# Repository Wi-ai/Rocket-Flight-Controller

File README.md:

# Rocket-Flight-Controller
this is a prototype flight controller for the rocket am building

Shipping price

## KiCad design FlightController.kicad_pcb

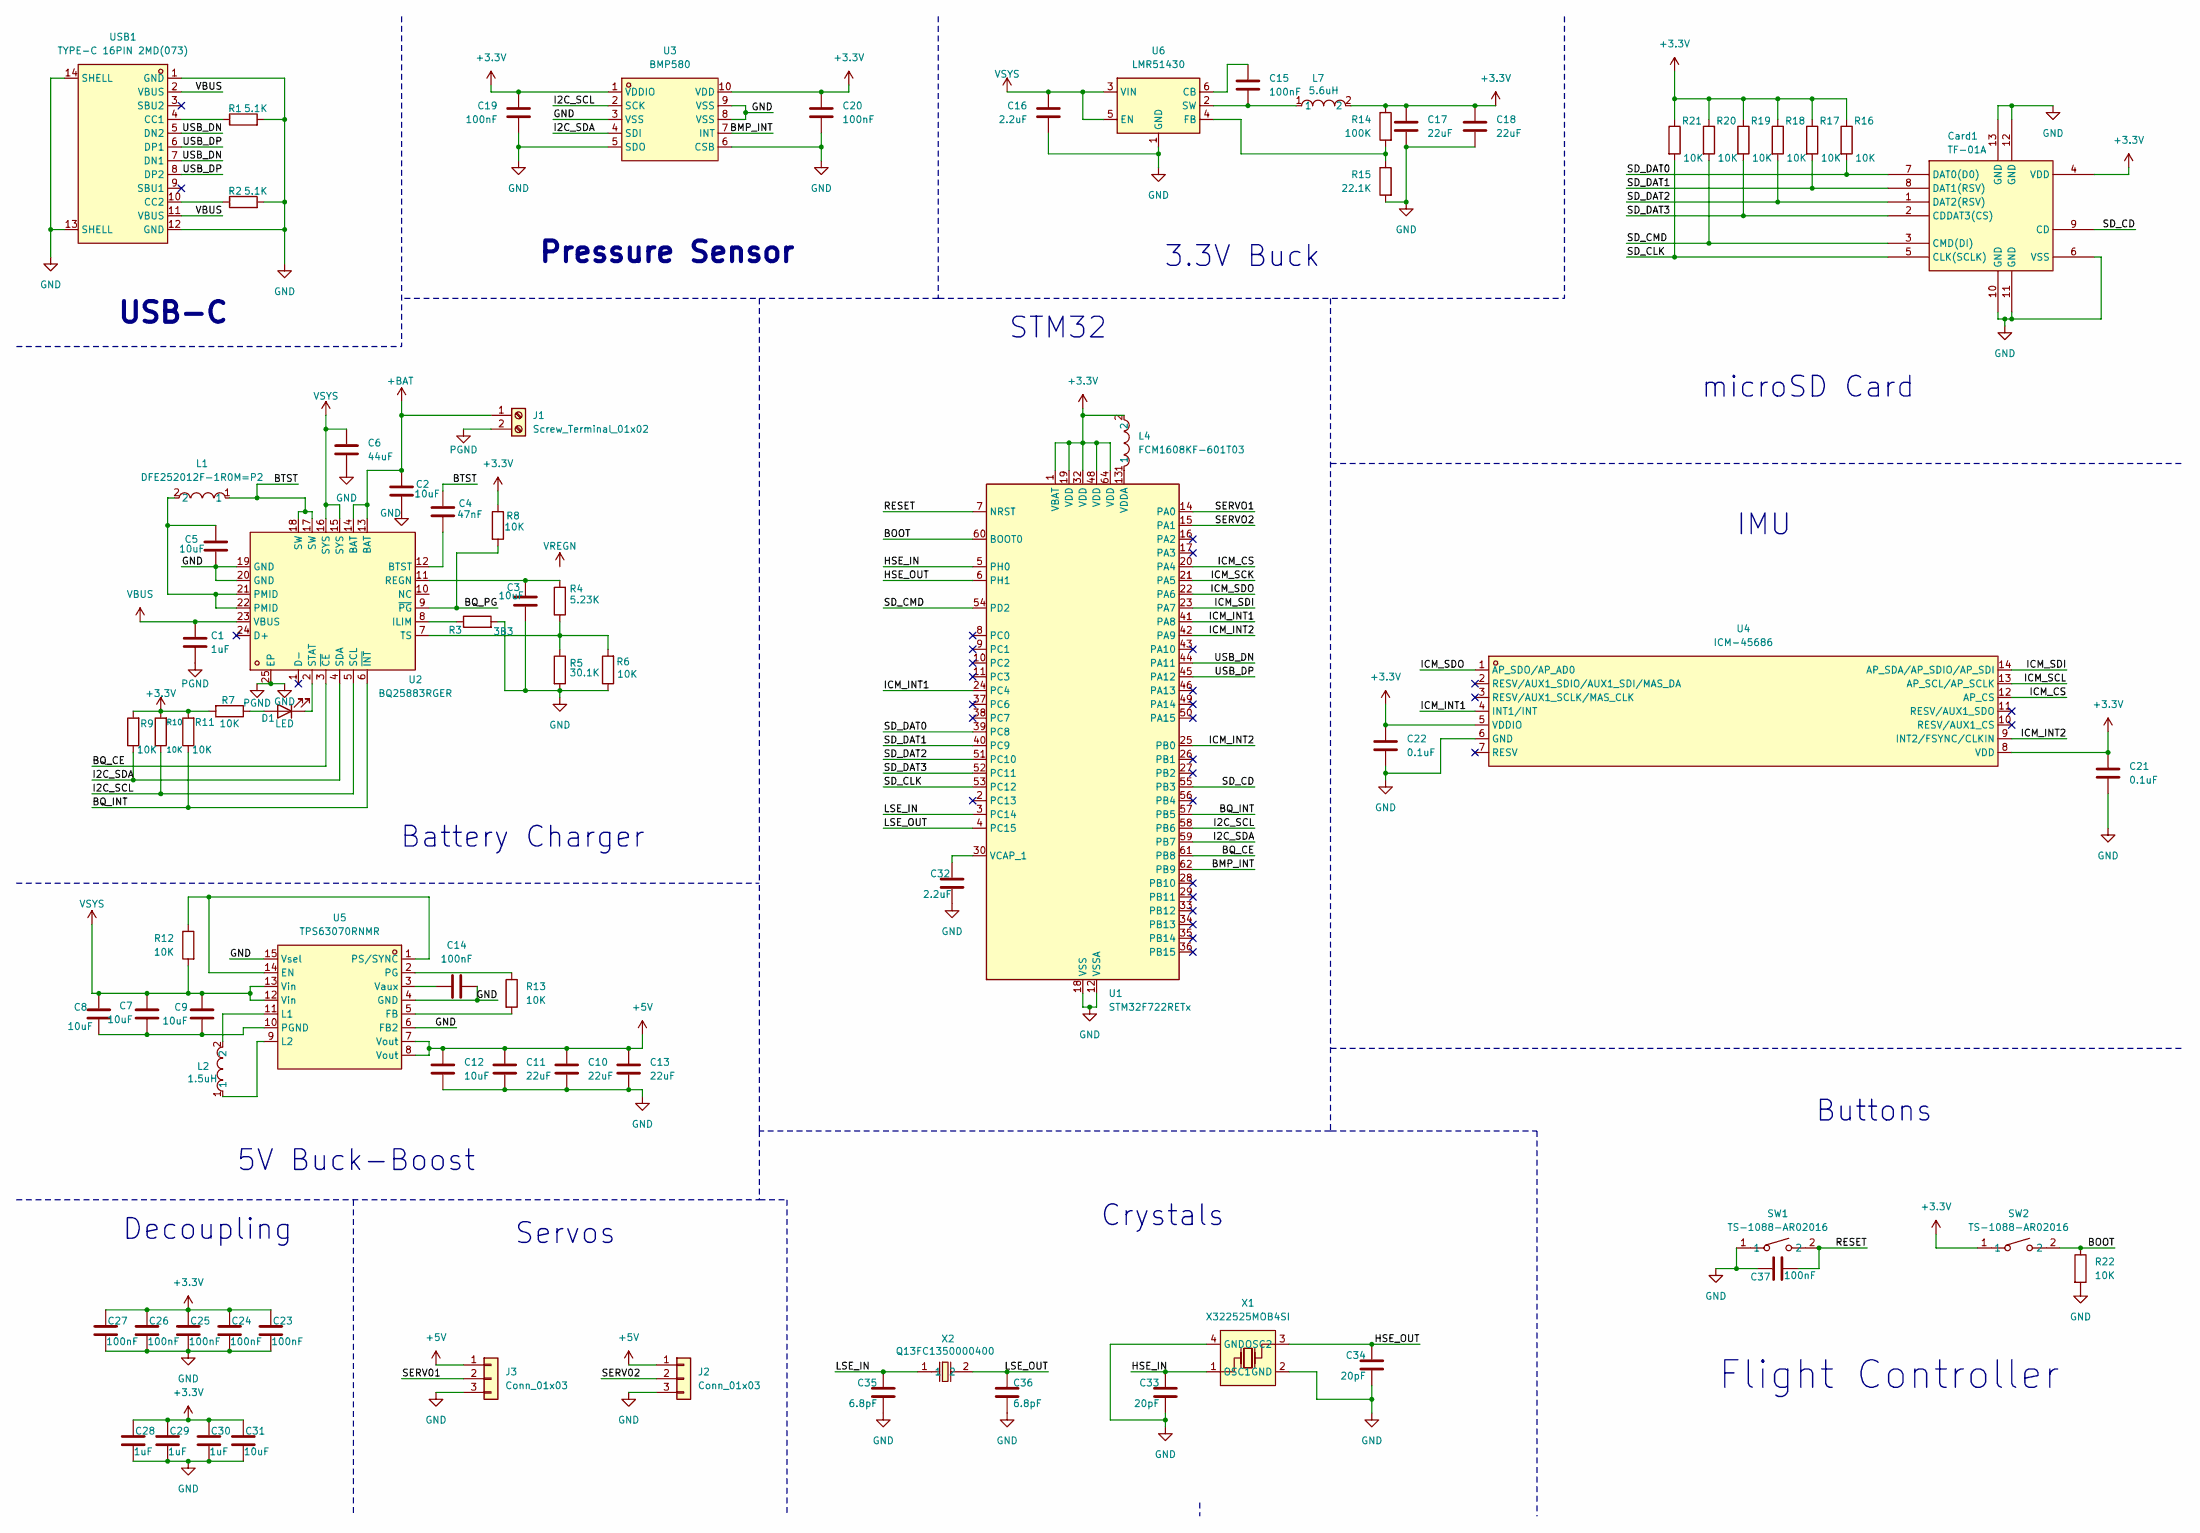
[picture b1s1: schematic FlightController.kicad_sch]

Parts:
C1, C28, C29, C30: 1uF; C_0402_1005Metric
C2, C9, C12: 10uF; C_0603_1608Metric
C3, C5, C31: 10uF; C_0402_1005Metric
C4: 47nF; C_0201_0603Metric
C6: 44uF; C_0603_1608Metric
C7, C8: 10uF; C_0805_2012Metric
C10, C11, C13: 22uF; C_0805_2012Metric
C14, C15, C19, C20, C23, C24, C25, C26, C27, C37: 100nF; C_0201_0603Metric
C16: 2.2uF; C_0603_1608Metric
C17, C18: 22uF; C_0402_1005Metric
C21, C22: 0.1uF; C_0201_0603Metric
C32: 2.2uF; C_0201_0603Metric
C33, C34: 20pF; C_0201_0603Metric
C35, C36: 6.8pF; C_0201_0603Metric
Card1: TF-01A; TF-SMD_TF-01A; LCSC Part C91145
D1: LED; LED_0402_1005Metric
J1: Screw_Terminal_01x02; TerminalBlock_Xinya_XY308-2.54-2P_1x02_P2.54mm_Horizontal
J2, J3: Conn_01x03; PinHeader_1x03_P2.54mm_Vertical
L1: DFE252012F-1R0M=P2; L2520; LCSC Part C435392
L2: 1.5uH; IND-SMD_L4.0-W4.0-A; LCSC Part C3033018
L4: FCM1608KF-601T03; L0603; LCSC Part C141723
L7: 5.6uH; IND-SMD_L3.0-W3.0; LCSC Part C18236327
R1, R2: 5.1K; R_0201_0603Metric
R3: 3B3; R_0201_0603Metric
R4: 5.23K; R_0201_0603Metric
R5: 30.1K; R_0201_0603Metric
R6, R7, R8, R9, R10, R11, R12, R13, R16, R17, R18, R19, R20, R21, R22: 10K; R_0201_0603Metric
R14: 100K; R_0402_1005Metric
R15: 22.1K; R_0402_1005Metric
SW1, SW2: TS-1088-AR02016; SW-SMD_L3.9-W3.0-P4.45; LCSC Part C720477
U1: STM32F722RETx; LQFP-64_10x10mm_P0.5mm
U2: BQ25883RGER; VFQFPN-24_L4.0-W4.0-P0.50-BL-EP2.8; LCSC Part C544362
U3: BMP580; LGA-10_L2.0-W2.0-P0.50-TL_BMP580; LCSC Part C22391138
U4: ICM-45686; LGA-14_L3.0-W2.5-P0.50-TL; LCSC Part C22459454
U5: TPS63070RNMR; VQFN-HR-15_L3.0-W2.5-P0.50-BL_TPS63070RNMR; LCSC Part C109322
U6: LMR51430; SOT-23-6
USB1: TYPE-C 16PIN 2MD(073); USB-C-SMD_TYPE-C-6PIN-2MD-073; LCSC Part C2765186
X1: X322525MOB4SI; CRYSTAL-SMD_4P-L3.2-W2.5-BL; LCSC Part C9006
X2: Q13FC1350000400; FC-135R_L3.2-W1.5; LCSC Part C32346

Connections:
+3.3V: C17.1, C18.1, C19.1, C20.1, C21.1, C22.1, C23.1, C24.1, C25.1, C26.1, C27.1, C28.1, C29.1, C30.1, C31.1, Card1.4 (VDD), L4.2, L7.2, R7.2, R8.1, R9.2, R10.2, R11.2, R14.1, R16.1, R17.1, R18.1, R19.1, R20.1, R21.1, SW2.1, U1.1 (VBAT), U1.19 (VDD), U1.32 (VDD), U1.48 (VDD), U1.64 (VDD), U3.1 (VDDIO), U3.10 (VDD), U4.5 (VDDIO), U4.8 (VDD)
+5V: C10.1, C11.1, C12.1, C13.1, J2.1, J3.1, U5.7 (Vout), U5.8 (Vout)
+BAT: C2.1, J1.1, U2.13 (BAT), U2.14 (BAT)
/BMP_INT: U1.62 (PB9), U3.7 (INT)
/BOOT: R22.1, SW2.2, U1.60 (BOOT0)
/BQ_CE: U1.61 (PB8), U2.3 (~CE)
/BQ_INT: R11.1, U1.57 (PB5), U2.6 (~INT)
/BQ_PG: R8.2, U2.9 (~PG)
/BTST: C4.1, L1.1, U2.17 (SW), U2.18 (SW)
/HSE_IN: C33.1, U1.5 (PH0), X1.1 (OSC1)
/HSE_OUT: C34.1, U1.6 (PH1), X1.3 (OSC2)
/I2C_SCL: R10.1, U1.58 (PB6), U2.5 (SCL), U3.2 (SCK)
/I2C_SDA: R9.1, U1.59 (PB7), U2.4 (SDA), U3.4 (SDI)
/ICM_CS: U1.20 (PA4), U4.12 (AP_CS)
/ICM_INT1: U1.24 (PC4), U1.41 (PA8), U4.4 (INT1/INT)
/ICM_INT2: U1.25 (PB0), U1.42 (PA9), U4.9 (INT2/FSYNC/CLKIN)
/ICM_SCK: U1.21 (PA5)
/ICM_SCL: U4.13 (AP_SCL/AP_SCLK)
/ICM_SDI: U1.23 (PA7), U4.14 (AP_SDA/AP_SDIO/AP_SDI)
/ICM_SDO: U1.22 (PA6), U4.1 (AP_SDO/AP_AD0)
/LSE_IN: C35.1, U1.3 (PC14), X2.1
/LSE_OUT: C36.1, U1.4 (PC15), X2.2
/RESET: C37.2, SW1.2, U1.7 (NRST)
/SD_CD: Card1.9 (CD), U1.55 (PB3)
/SD_CLK: Card1.5 (CLK(SCLK)), R21.2, U1.53 (PC12)
/SD_CMD: Card1.3 (CMD(DI)), R20.2, U1.54 (PD2)
/SD_DAT0: Card1.7 (DAT0(D0)), R16.2, U1.39 (PC8)
/SD_DAT1: Card1.8 (DAT1(RSV)), R17.2, U1.40 (PC9)
/SD_DAT2: Card1.1 (DAT2(RSV)), R18.2, U1.51 (PC10)
/SD_DAT3: Card1.2 (CDDAT3(CS)), R19.2, U1.52 (PC11)
/SERV01: J3.2
/SERV02: J2.2
/SERVO1: U1.14 (PA0)
/SERVO2: U1.15 (PA1)
/USB_DN: U1.44 (PA11), USB1.5 (DN2), USB1.7 (DN1)
/USB_DP: U1.45 (PA12), USB1.6 (DP1), USB1.8 (DP2)
GND: C1.2, C2.2, C3.2, C5.2, C6.2, C10.2, C11.2, C12.2, C13.2, C14.2, C16.2, C17.2, C18.2, C19.2, C20.2, C21.2, C22.2, C23.2, C24.2, C25.2, C26.2, C27.2, C28.2, C29.2, C30.2, C31.2, C32.2, C33.2, C34.2, C35.2, C36.2, C37.1, Card1.6 (VSS), Card1.10 (GND), Card1.11 (GND), Card1.12 (GND), Card1.13 (GND), J1.2, J2.3, J3.3, R1.2, R2.2, R3.2, R5.2, R6.1, R15.2, R22.2, SW1.1, U1.12 (VSSA), U1.18 (VSS), U1.31 (VSS), U1.47 (VSS), U1.63 (VSS), U2.19 (GND), U2.20 (GND), U2.25 (EP), U3.3 (VSS), U3.5 (SDO), U3.6 (CSB), U3.8 (VSS), U3.9 (VSS), U4.6 (GND), U5.4 (GND), U5.6 (FB2), U5.15 (Vsel), U6.1 (GND), USB1.1 (GND), USB1.12 (GND), USB1.13 (SHELL), USB1.14 (SHELL), X1.2 (GND), X1.4 (GND)
unnamed: C5.1, L1.2, U2.21 (PMID), U2.22 (PMID)
unnamed: D1.2 (A), R7.1
unnamed: D1.1 (K), U2.2 (STAT)
unnamed: C32.1, U1.30 (VCAP_1)
unnamed: L4.1, U1.13 (VDDA)
unnamed: C4.2, U2.12 (BTST)
unnamed: R3.1, U2.8 (ILIM)
unnamed: C3.1, R4.2, U2.11 (REGN)
unnamed: R4.1, R5.1, R6.2, U2.7 (TS)
unnamed: R12.1, U5.1 (PS/SYNC), U5.14 (EN)
unnamed: R13.2, U5.5 (FB)
unnamed: L2.2, U5.11 (L1)
unnamed: L2.1, U5.9 (L2)
unnamed: R13.1, U5.2 (PG)
unnamed: C7.2, C8.2, C9.2, U5.10 (PGND)
unnamed: C14.1, U5.3 (Vaux)
unnamed: C15.1, U6.6 (CB)
unnamed: R14.2, R15.1, U6.4 (FB)
unnamed: C15.2, L7.1, U6.2 (SW)
unnamed: R1.1, USB1.4 (CC1)
unnamed: R2.1, USB1.10 (CC2)
VBUS: C1.1, U2.23 (VBUS), USB1.2 (VBUS), USB1.11 (VBUS)
VSYS: C6.1, C7.1, C8.1, C9.1, C16.1, R12.2, U2.15 (SYS), U2.16 (SYS), U5.12 (Vin), U5.13 (Vin), U6.3 (VIN), U6.5 (EN)

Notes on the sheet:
Buttons
Pressure Sensor
Battery Charger
IMU
USB-C
5V Buck-Boost
3.3V Buck
Decoupling
Servos
Flight Controller
Crystals
microSD Card
STM32

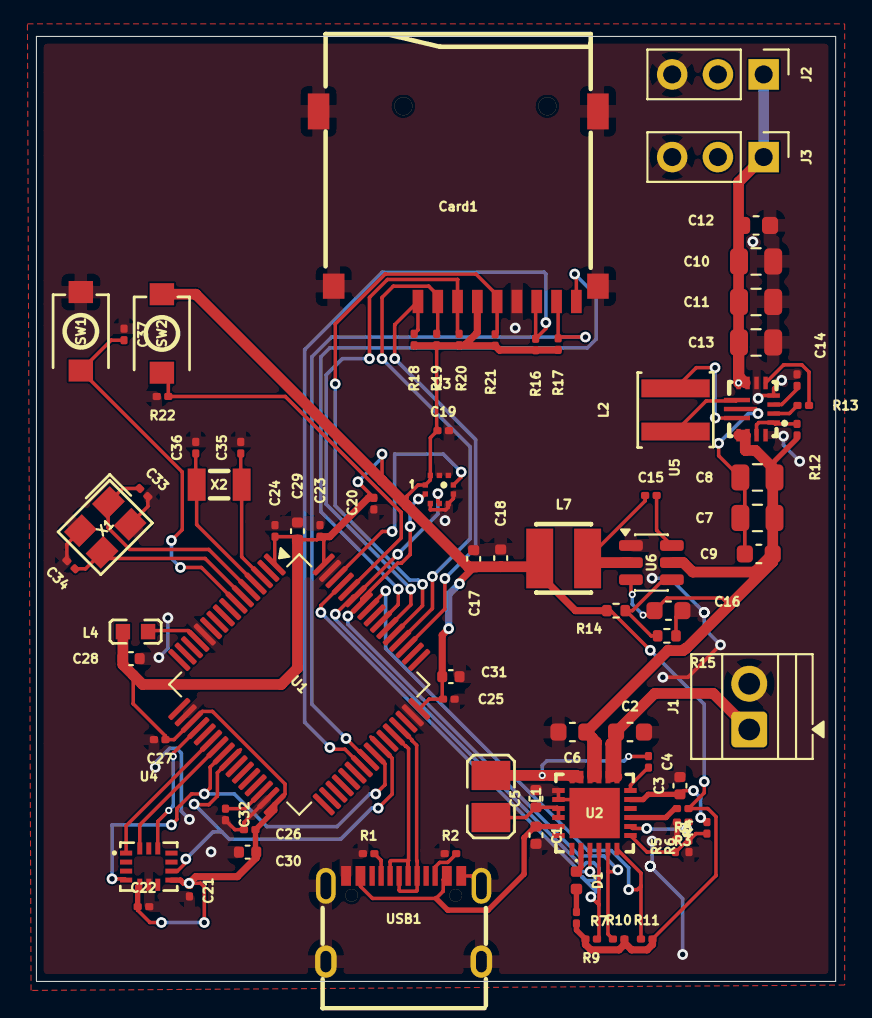
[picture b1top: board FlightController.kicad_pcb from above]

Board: 2 copper layers, 44.4 x 52.5 mm, 79 parts (0 on the bottom side), 54 nets.

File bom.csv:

Designator,Footprint,Quantity,Value,LCSC Part #
"C1, C28, C29, C30",0402,4,1uF,
"C10, C11, C13",0805,3,22uF,
"C12, C2, C9",0603,3,10uF,
"C14, C15, C19, C20, C23, C24, C25, C26, C27, C37",0201,10,100nF,
C16,0603,1,2.2uF,
"C17, C18",0402,2,22uF,
"C21, C22",0201,2,0.1uF,
"C3, C31, C5",0402,3,10uF,
C32,0201,1,2.2uF,
"C33, C34",0201,2,20pF,
"C35, C36",0201,2,6.8pF,
C4,0201,1,47nF,
C6,0603,1,44uF,
"C7, C8",0805,2,10uF,
CARD1,TF-SMD_TF-01A,1,TF-01A,C91145
D1,0402,1,LED,
J1,TerminalBlock_Xinya_XY308-2.54-2P_1x02_P2.54mm_Horizontal,1,Screw_Terminal_01x02,
"J2, J3",PinHeader_1x03_P2.54mm_Vertical,2,Conn_01x03,
L1,L2520,1,DFE252012F-1R0M=P2,C435392
L2,IND-SMD_L4.0-W4.0-A,1,1.5uH,C3033018
L4,L0603,1,FCM1608KF-601T03,C141723
L7,IND-SMD_L3.0-W3.0,1,5.6uH,C18236327
"R1, R2",0201,2,5.1K,
"R10, R11, R12, R13, R16, R17, R18, R19, R20, R21, R22, R6, R7, R8, R9",0201,15,10K,
R14,0402,1,100K,
R15,0402,1,22.1K,
R3,0201,1,3B3,
R4,0201,1,5.23K,
R5,0201,1,30.1K,
"SW1, SW2",SW-SMD_L3.9-W3.0-P4.45,2,TS-1088-AR02016,C720477
U1,LQFP-64_10x10mm_P0.5mm,1,STM32F722RETx,
U2,VFQFPN-24_L4.0-W4.0-P0.50-BL-EP2.8,1,BQ25883RGER,C544362
U3,LGA-10_L2.0-W2.0-P0.50-TL_BMP580,1,BMP580,C22391138
U4,LGA-14_L3.0-W2.5-P0.50-TL,1,ICM-45686,C22459454
U5,VQFN-HR-15_L3.0-W2.5-P0.50-BL_TPS63070RNMR,1,TPS63070RNMR,C109322
U6,SOT-23-6,1,LMR51430,
USB1,USB-C-SMD_TYPE-C-6PIN-2MD-073,1,TYPE-C 16PIN 2MD(073),C2765186
X1,CRYSTAL-SMD_4P-L3.2-W2.5-BL,1,X322525MOB4SI,C9006
X2,FC-135R_L3.2-W1.5,1,Q13FC1350000400,C32346
